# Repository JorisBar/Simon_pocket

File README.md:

# Simon_pocket – A pocket version of the classic Simon says game

**Simon_pocket is a pocket sized memory training game. Players have to repeat a button sequence that gets longer each round. This project includes a custom PCB, bare metal programming for an STM32 MCU and a 3D printed housing.**

---

## Gameplay

---

## Hardware Architecture

---

## Component Selection and Design Considerations

- **Microcontroller:** The STM32F030C6T6 was chosen for being inexpensive (0.5€ @ 30+ Qty) and having good documentation and support.
- **Battery:** The CR2032 was selected because of the 3V nominal voltage, compact size and availability.
- **Sound system:** Buzzers/speakers had to be omitted due to the high internal resistance of the battery.
- **Power on:** Due to space constraints, a dedicated power button was not possible. Instead, every button is configured to wake up the MCU from STOP mode.
- **Standby current:** To decrease standby current to ~6uA:
  - A low leakage current PMOS was selected.
  - No LDOs or switching regulators were used.
  - The MCU operates mostly in STOP power saving mode.

---

## PCB Design & Layout Details

### Layer Stackup (2-Layer)
1. **Top (Signal / Power):** MCU, LED and button traces. Power distribution.
2. **Bottom (Ground / Power):** Negative battery contact and ground plane. Power distribution.

### PCB panel
A PCB panel was designed to decrease the cost of each PCB.

---

## Programming
The code was written in bare metal CMSIS C using the STM32CubeIDE. To upload the code an ST-LINK V2 has to be connected to the programming contacts on the PCB.

### Code structure

### State machine transitions

---
## 3D modeling and printing
The housing was modeled using Autodesk Fusion. It was printed using a Bambu Lab A1 mini 3D printer.

---

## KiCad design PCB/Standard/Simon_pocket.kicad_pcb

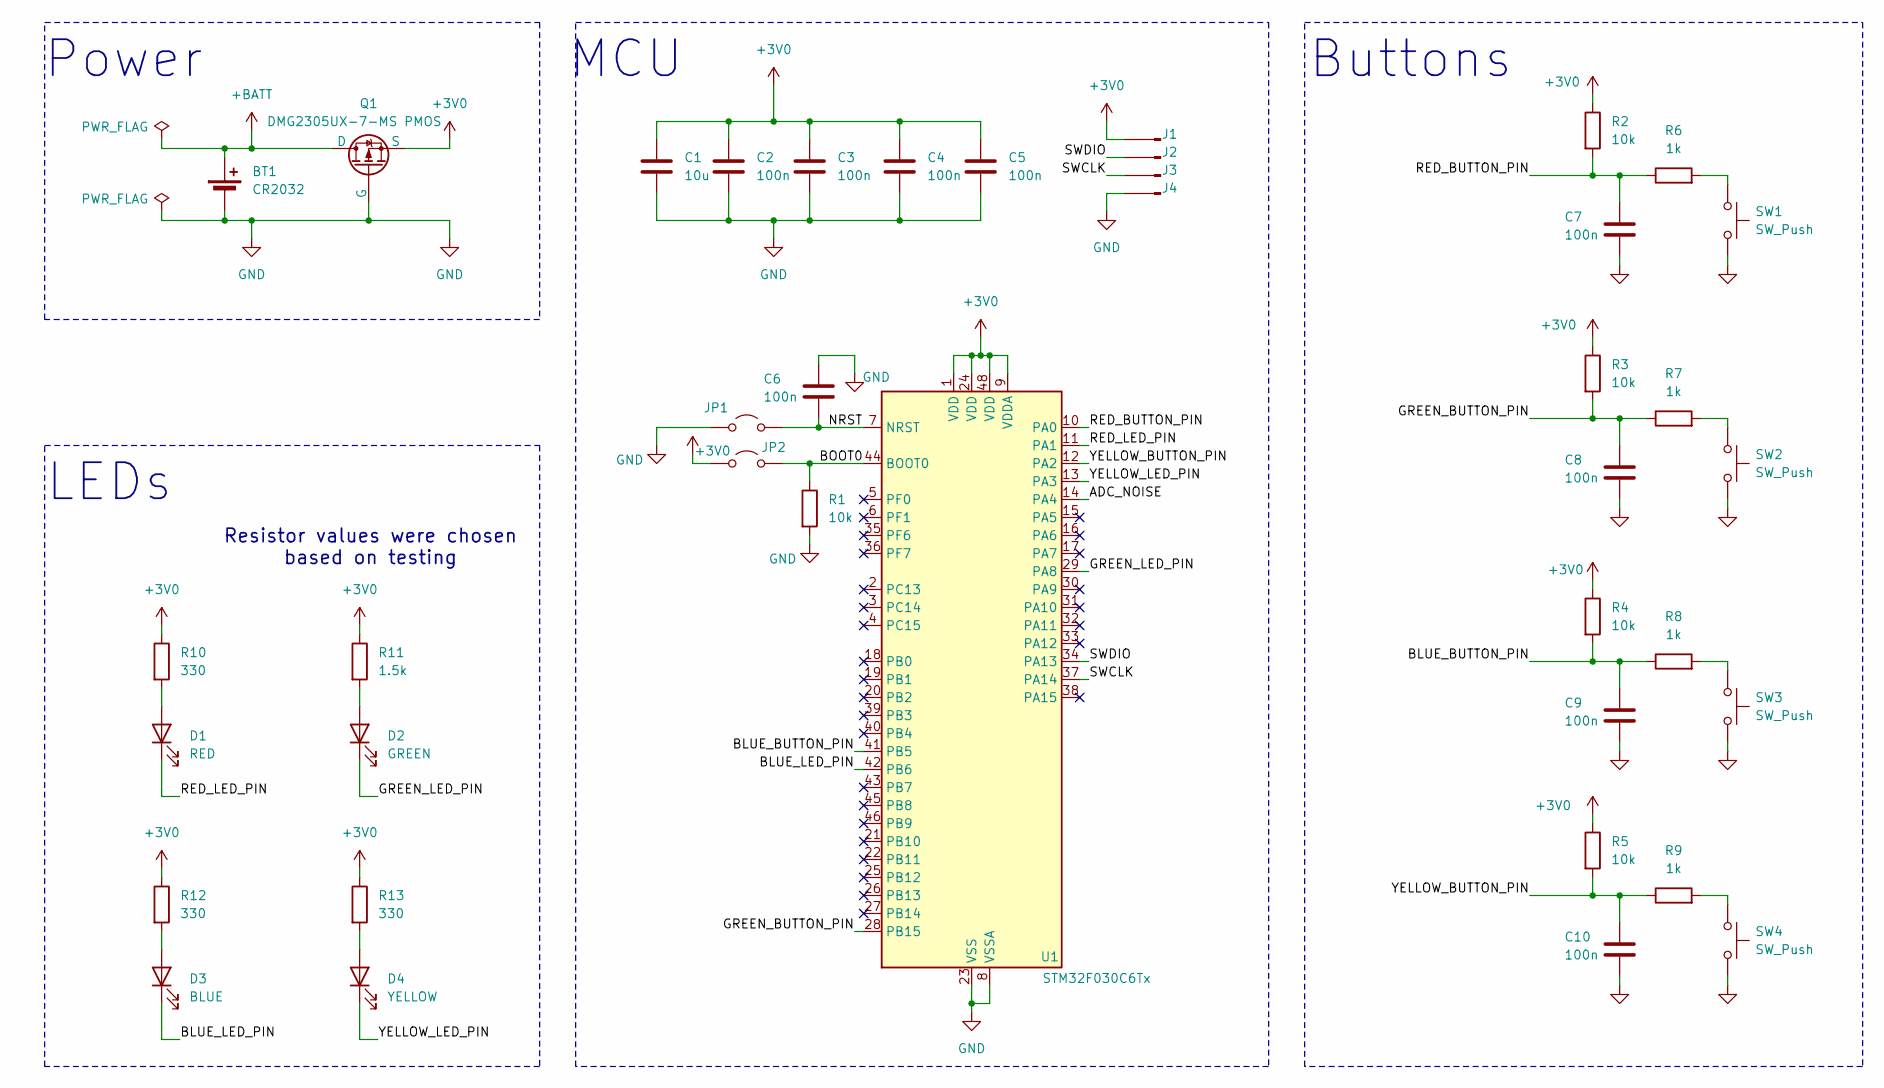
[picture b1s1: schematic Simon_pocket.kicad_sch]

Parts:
BT1: CR2032; CR2032 slim holder; LCSC PN C2902340
C1: 10u; C_0603_1608Metric; LCSC PN C6119842
C2, C3, C4, C5, C6, C7, C8, C9, C10: 100n; C_0603_1608Metric; LCSC PN C6119867
D1: RED; LED_0603_1608Metric; LCSC PN C965799
D2: GREEN; LED_0603_1608Metric; LCSC PN C51933293
D3: BLUE; LED_0603_1608Metric; LCSC PN C51933294
D4: YELLOW; LED_0603_1608Metric; LCSC PN C51933295
J1, J2, J3, J4: Conn_01x01_Pin; TestPoint_Pad_1.0x1.0mm
JP1, JP2: Jumper_2_Open; SolderJumper-2_P1.3mm_Open_RoundedPad1.0x1.5mm
Q1: DMG2305UX-7-MS PMOS; SOT-23; LCSC PN C7379997
R1, R2, R3, R4, R5: 10k; R_0603_1608Metric; LCSC PN C49652949
R6, R7, R8, R9: 1k; R_0603_1608Metric; LCSC PN C2907002
R10, R12, R13: 330; R_0603_1608Metric; LCSC PN C49653542
R11: 1.5k; R_0603_1608Metric; LCSC PN C2930050
SW1, SW2, SW3, SW4: SW_Push; SW_Push mini square HansElectricity C22375378; LCSC PN C22375378
U1: STM32F030C6Tx; LQFP-48_7x7mm_P0.5mm; LCSC PN C106925

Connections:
+3V0: C1.1, C2.1, C3.1, C4.1, C5.1, J1.1 (Pin_1_1), JP2.1 (A), Q1.2 (S), R2.1, R3.1, R4.1, R5.1, R10.1, R11.1, R12.1, R13.1, U1.1 (VDD), U1.9 (VDDA), U1.24 (VDD), U1.48 (VDD)
+BATT: BT1.1 (+), Q1.3 (D)
/ADC_NOISE: U1.14 (PA4)
/BLUE_BUTTON_PIN: C9.1, R4.2, R8.1, U1.41 (PB5)
/BLUE_LED_PIN: D3.1 (K), U1.42 (PB6)
/BOOT0: JP2.2 (B), R1.1, U1.44 (BOOT0)
/GREEN_BUTTON_PIN: C8.1, R3.2, R7.1, U1.28 (PB15)
/GREEN_LED_PIN: D2.1 (K), U1.29 (PA8)
/NRST: C6.2, JP1.2 (B), U1.7 (NRST)
/RED_BUTTON_PIN: C7.1, R2.2, R6.1, U1.10 (PA0)
/RED_LED_PIN: D1.1 (K), U1.11 (PA1)
/SWCLK: J3.1 (Pin_1_1), U1.37 (PA14)
/SWDIO: J2.1 (Pin_1_1), U1.34 (PA13)
/YELLOW_BUTTON_PIN: C10.1, R5.2, R9.1, U1.12 (PA2)
/YELLOW_LED_PIN: D4.1 (K), U1.13 (PA3)
GND: BT1.2 (-), C1.2, C2.2, C3.2, C4.2, C5.2, C6.1, C7.2, C8.2, C9.2, C10.2, J4.1 (Pin_1_1), JP1.1 (A), Q1.1 (G), R1.2, SW1.2, SW2.2, SW3.2, SW4.2, U1.8 (VSSA), U1.23 (VSS), U1.47 (VSS)
unnamed: D1.2 (A), R10.2
unnamed: D2.2 (A), R11.2
unnamed: D3.2 (A), R12.2
unnamed: D4.2 (A), R13.2
unnamed: R6.2, SW1.1
unnamed: R7.2, SW2.1
unnamed: R8.2, SW3.1
unnamed: R9.2, SW4.1

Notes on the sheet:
LEDs
Resistor values were chosen based on testing
Buttons
MCU
Power

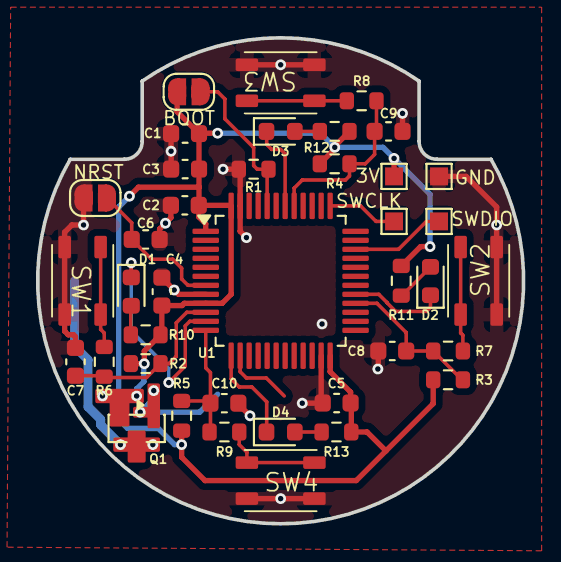
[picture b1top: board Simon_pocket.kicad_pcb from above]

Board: 2 copper layers, 27.0 x 27.0 mm, 40 parts (1 on the bottom side), 23 nets.

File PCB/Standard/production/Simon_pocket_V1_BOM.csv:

"Reference","Qty","Value","Footprint","LCSC PN"
"BT1","1","CR2032","My library:CR2032 slim holder","C2902340"
"C1","1","10u","Capacitor_SMD:C_0603_1608Metric","C6119842"
"C2,C3,C4,C5,C6,C7,C8,C9,C10","9","100n","Capacitor_SMD:C_0603_1608Metric","C6119867"
"D1","1","RED","LED_SMD:LED_0603_1608Metric","C965799"
"D2","1","GREEN","LED_SMD:LED_0603_1608Metric","C51933293"
"D3","1","BLUE","LED_SMD:LED_0603_1608Metric","C51933294"
"D4","1","YELLOW","LED_SMD:LED_0603_1608Metric","C51933295"
"Q1","1","DMG2305UX-7-MS PMOS","Package_TO_SOT_SMD:SOT-23","C7379997"
"R1,R2,R3,R4,R5","5","10k","Resistor_SMD:R_0603_1608Metric","C49652949"
"R6,R7,R8,R9","4","1k","Resistor_SMD:R_0603_1608Metric","C2907002"
"R10,R12,R13","3","330","Resistor_SMD:R_0603_1608Metric","C49653542"
"R11","1","1.5k","Resistor_SMD:R_0603_1608Metric","C2930050"
"SW1,SW2,SW3,SW4","4","SW_Push","My library:SW_Push mini square HansElectricity C22375378","C22375378"
"U1","1","STM32F030C6Tx","Package_QFP:LQFP-48_7x7mm_P0.5mm","C106925"
